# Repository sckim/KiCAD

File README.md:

# KiCad 튜토리얼
대학교 2학년 학생이 KiCad 사용법을 익힐 수 있도록 만든 예제 모음이다. 자세한 설명은 [이 문서](https://docs.google.com/document/d/1ExvIu8tnpRs45NydWLtySDykhyoZ8oFFZSsFo3mHvT8/edit?tab=t.0#heading=h.j3pbzu6m0ixx)를 참고한다.

- 모든 예제는 **KiCad 10** 기준이다.
- 각 예제 폴더에 README가 있다. 번호 순서대로 따라가면 된다.
- KiCad 공식 설명서는 [Docs](./Docs/)에 있다. 처음이라면 *Getting Started in KiCad* 부터 읽는다.

| 폴더 | 내용 |
|---|---|
| [10_Simple_LED](./10_Simple_LED/) | 첫 예제. 회로도에서 PCB, 거버 출력까지 |
| [20_WheatstoneBridge](./20_WheatstoneBridge/) | 회로 시뮬레이션과 PCB를 하나의 회로도로 |
| [22_4bitsFullAdder](./22_4bitsFullAdder/) | 계층 회로도, 논리 IC 보드 |
| [30_Arduino](./30_Arduino/) | Arduino UNO 템플릿과 관련 보드 |
| [70_Simulation](./70_Simulation/) | SPICE 시뮬레이션 전용 예제 |
| [Applications](./Applications/) | 응용 예제(실험 키트, 외부 PCB 가져오기) |
| [Docs](./Docs/) | KiCad 공식 설명서 |

---

## 1. 기본 PCB 예제

### [예제 1. Simple LED](./10_Simple_LED/)
코인 전지로 LED를 켜는 가장 간단한 회로이다. 회로도 작성 → 풋프린트 지정 → PCB 배치·배선 → 거버 출력까지 KiCad의 전체 흐름을 익힌다.
<table>
    <tr>
        <td></td>
        <td></td>
    </tr>
</table>

### [예제 2. Wheatstone Bridge](./20_WheatstoneBridge/)
휘트스톤 브리지를 SPICE로 시뮬레이션하고 PCB로 만든다. 시뮬레이션 전용 부품과 PCB 전용 부품을 한 회로도에서 나누어 쓰는 방법(Exclude from simulation / board)을 익힌다.
<table>
    <tr>
        <td></td>
        <td></td>
    </tr>
</table>

### [예제 3. 4bits Full Adder](./22_4bitsFullAdder/)
반가산기 → 전가산기 → 4비트 덧셈기로 올라가며 **계층 회로도** 를 익힌다. 입력 스위치, 출력 LED, 전원까지 넣어 실제 보드로 만들고, 배선 실습용 PCB와 자동 배선 완성본을 함께 제공한다.
<table>
    <tr><td colspan="2"></td></tr>
    <tr><td colspan="2"></td></tr>
    <tr><td></td><td></td></tr>
</table>

---

## 2. Arduino

### 심볼·풋프린트 편집기: [Arduino_UNO](./30_Arduino/Arduino_UNO/)
KiCad 템플릿으로 Arduino UNO 쉴드의 외곽과 헤더를 만든다.
<table>
    <tr>
        <td></td>
        <td></td>
    </tr>
</table>

### Arduino 관련 프로젝트
[30_Arduino](./30_Arduino/) 폴더에 모아 두었다.
* [Arduino UNO (ATmega328P)](./30_Arduino/UNO_ATmega328P/): Arduino_UNO 템플릿으로 만든 UNO 호환 보드(ATmega328P, 크리스털, 리셋, ICSP, PCB)
* [Arduino UNO I2C LCD](./30_Arduino/Arduino_UNO_I2C_LCD/): Arduino UNO에서 PCF8574 I2C 확장 칩으로 16×2 LCD를 구동하는 회로(회로도만)
* [nRF52840 UNO](./30_Arduino/nRF52840_UNO/): Adafruit Feather nRF52840 Express를 Arduino UNO 레이아웃에 맞춘 보드

---

## 3. 시뮬레이션
PCB 없이 회로도와 시뮬레이션만 다루는 예제를 [70_Simulation](./70_Simulation/)에 모아 두었다. 예제마다 README가 있다.
* [Transient Analysis](./70_Simulation/Transient_Analysis/): 펄스 전원으로 구동하는 RC 회로의 충전과 방전 (`.tran`)
* [Frequency Analysis](./70_Simulation/Frequency_Analysis/): RC 저역통과 필터와 CR 고역통과 필터 비교 (`.ac`)
* [AC Analysis](./70_Simulation/AC_Analysis/): 직렬 RLC 대역통과 필터 (`.ac`)
* [Transistor Bias](./70_Simulation/TransistorBias/): 제조사 2N3904 모델을 쓴 BJT 동작점 (`.op`)
* [Half Adder](./70_Simulation/HalfAdder/): [SpiceModels](./70_Simulation/SpiceModels/)의 74LS 모델을 쓴 디지털 시뮬레이션 (`.tran`)

---

## 4. 응용 예제

### [Analog Discovery 2와 UNO 또는 Adafruit nRF52 Bluefruit 연결](./Applications/Arduino_AD2Kit/)
<table>
    <tr>
        <td></td>
        <td></td>
    </tr>
</table>

### 외부 PCB 가져오기
* [Adafruit nRF52 Bluefruit Feather](./Applications/Adafruit_nRF52_Bluefruit/): [Eagle PCB](https://github.com/adafruit/Adafruit-nRF52-Bluefruit-Feather-PCB)와 [3D 모델](https://github.com/adafruit/Adafruit_CAD_Parts/tree/main/4062%20nRF52840%20Feather)을 KiCad로 가져온 예제

### Texas Instruments EVM 보드 확장
(준비 중)

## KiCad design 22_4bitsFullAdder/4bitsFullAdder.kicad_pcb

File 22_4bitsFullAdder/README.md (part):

# 예제 3. 4bits Full Adder — 계층 회로도(Hierarchical Schematic)

4비트 덧셈기를 만들면서 **계층 회로도**를 익힌다.
반가산기(Half Adder)를 한 장의 시트로 만들고, 이를 두 번 써서 전가산기(Full Adder)를 만든 다음, 전가산기를 네 번 써서 4비트 덧셈기를 만든다.
같은 회로를 여러 번 복사해 그리지 않고 **한 번 그린 시트를 재사용**하는 것이 핵심이다.

<table>
    <tr><td colspan="2"></td></tr>
    <tr><td colspan="2"></td></tr>
    <tr><td></td><td></td></tr>
</table>

> 이 예제는 [예제 1](../10_Simple_LED/)을 마쳤다고 가정한다. 회로도 작성의 기본 조작(심볼 배치, 배선, 레이블)은 예제 1을 참고한다.
> 회로도에는 입력 스위치, 출력 LED, 전원까지 들어 있고, PCB는 부품 배치와 넷 연결까지 되어 있다. **배선은 직접 해 본다**([6장](#6-실제-보드로-만들기)).

---

## 1. 폴더 구성

| 파일 | 설명 |
|---|---|
| `4bitsFullAdder.kicad_pro` | 프로젝트 파일이다. 이 파일을 연다. |
| `4bitsFullAdder.kicad_sch` | **최상위(root) 시트**. 전가산기 시트 4개(`FA0`~`FA3`)와 입출력 버스, 그리고 전원·입력 스위치·출력 LED 회로가 있다. |
| `FullAdder.kicad_sch` | **전가산기 시트**. 반가산기 시트 2개(`HA1`, `HA2`)와 OR 게이트(74HC32)로 이루어진다. |
| `HalfAdder.kicad_sch` | **반가산기 시트**. AND 게이트(74HC08)와 XOR 게이트(74HC86)로 이루어진다. |
| `4bitsFullAdder.kicad_pcb` | PCB. 부품 배치와 넷 연결까지 되어 있고 배선은 되어 있지 않다. |

## 2. 덧셈기의 원리

### 2-1. 반가산기 (Half Adder)
1비트 두 개(A, B)를 더해 합(S)과 올림(C)을 낸다.

| A | B | S (합) | C (올림) |
|---|---|---|---|
| 0 | 0 | 0 | 0 |
| 0 | 1 | 1 | 0 |
| 1 | 0 | 1 | 0 |
| 1 | 1 | 0 | 1 |

```
S = A ⊕ B   (XOR, 74HC86)
C = A · B   (AND, 74HC08)
```

### 2-2. 전가산기 (Full Adder)
아랫자리에서 올라온 올림(Cin)까지 1비트 세 개를 더한다. 반가산기 2개와 OR 게이트 1개로 만든다.

```
HA1:  S1 = A ⊕ B,        C1 = A · B
HA2:  Sum = S1 ⊕ Cin,    C2 = S1 · Cin
Carry = C1 + C2          (OR, 74HC32)
```

```
 A ──┐         S1 ┌─────┐ S ──────────────── Sum
     │ HA1 ├──────┤ HA2 │
 B ──┘     │  Cin ─┤     │ C ──┐
           │       └─────┘     ├── OR ─────── Carry
           └── C1 ─────────────┘
```

### 2-3. 4비트 덧셈기 (Ripple Carry Adder)
전가산기 4개를 이어 붙여, 각 자리의 올림(Carry)을 다음 자리의 Cin으로 넘긴다.

```
          A0 B0      A1 B1      A2 B2      A3 B3
           │  │       │  │       │  │       │  │
 GND(0) → [ FA0 ] → [ FA1 ] → [ FA2 ] → [ FA3 ] → Carry (최종 올림)
             │          │          │          │
           Sum0       Sum1       Sum2       Sum3
```

- 맨 아랫자리 `FA0`의 Cin은 `GND`(0)에 연결한다.
- 올림이 오른쪽 자리로 차례차례 전달된다고 해서 **리플 캐리(ripple carry) 덧셈기**라고 부른다.

---

## 3. 계층 회로도 이해하기

### 3-1. 시트 구조
```
4bitsFullAdder.kicad_sch  (최상위)
├── FA0 ─ FullAdder.kicad_sch ─┬─ HA1 ─ HalfAdder.kicad_sch
│                              └─ HA2 ─ HalfAdder.kicad_sch
├── FA1 ─ FullAdder.kicad_sch   (같은 구조)
├── FA2 ─ FullAdder.kicad_sch   (같은 구조)
└── FA3 ─ FullAdder.kicad_sch   (같은 구조)
```
시트 **파일**은 3개뿐이지만 시트 **인스턴스(사용 횟수)** 는 최상위 1 + 전가산기 4 + 반가산기 8 = 13개이다.

### 3-2. 핵심 개념

| 개념 | 설명 | 이 예제에서 |
|---|---|---|
| **시트 기호 (Sheet Symbol)** | 상위 시트에 놓는 사각형 상자이다. 하위 시트 파일을 가리킨다. | 최상위의 `FA0`~`FA3`, 전가산기 안의 `HA1`, `HA2` |
| **계층 레이블 (Hierarchical Label)** | 하위 시트 안에서 "이 신호를 밖으로 내보낸다/받는다"를 나타낸다. | 반가산기의 `A`, `B`, `S`, `C` / 전가산기의 `A`, `B`, `C`, `Sum`, `Carry` |
| **시트 핀 (Sheet Pin)** | 시트 기호 테두리에 나타나는 핀이다. 하위 시트의 계층 레이블과 **이름이 같아야** 연결된다. | 시트 기호 양옆의 입력/출력 핀 |
| **버스 (Bus)** | 여러 신호를 하나의 굵은 선으로 묶는다. `A[3..0]`은 `A0`, `A1`, `A2`, `A3` 네 신호를 뜻한다. | 최상위의 `A[3..0]`, `B[3..0]`, `Sum[3..0]` |
| **버스 엔트리 (Bus Entry)** | 버스에서 개별 신호를 꺼내는 짧은 사선이다. 꺼낸 선에는 `A0` 같은 레이블을 붙인다. | 최상위의 12개 |

### 3-3. 시트 재사용과 부품 번호
같은 시트 파일을 여러 번 쓰면 **회로는 하나를 공유하지만 부품 번호는 인스턴스마다 따로** 붙는다.
예를 들어 `HalfAdder.kicad_sch`의 AND 게이트는 한 번만 그렸지만, 8개 인스턴스는 각각 다른 IC와 게이트(unit)에 배정된다.

| 인스턴스 | AND (74HC08) | XOR (74HC86) |
|---|---|---|
| FA0 / HA1, HA2 | U1A, U1B | U3A, U3B |
| FA1 / HA1, HA2 | U1C, U1D | U3C, U3D |
| FA2 / HA1, HA2 | U2A, U2B | U4A, U4B |
| FA3 / HA1, HA2 | U2C, U2D | U4C, U4D |

전가산기의 OR 게이트 4개는 `U5A`~`U5D`(74HC32)이다. 한 IC에 게이트가 4개씩 들어 있으므로 게이트 20개가 **IC 5개**에 담긴다. 각 IC의 전원 핀(VCC 14번, GND 7번)은 별도 unit `E`로, 최상위 시트에 배치되어 있다.
그래서 반가산기 시트를 고치면 **8곳 모두에 한꺼번에 반영된다.**

---

## 4. 예제 살펴보기

1. `4bitsFullAdder.kicad_pro`를 열고 회로도 편집기를 연다.
2. 왼쪽 **계층 탐색기(Hierarchy Navigator)** 에서 시트 트리를 확인한다. 보이지 않으면 **View → Show Hierarchy Navigator** 를 켠다.
3. 시트 기호(`FA0`)를 **더블클릭**하면 하위 시트로 들어간다. 계층 탐색기에서 최상위를 클릭하면 다시 올라온다.
4. `FA0` 안의 `HA1`로 들어가 부품 번호를 확인하고, 다시 나와 `FA1` 안의 `HA1`로 들어가 번호가 다른지 비교한다.
5. 한 신호가 어디로 이어지는지 보려면 선을 클릭한 뒤 **`` ` `` (백틱) 키**로 넷 전체를 강조 표시한다.

---

## 5. 처음부터 직접 만들어 보기

아래(반가산기)에서 위(4비트)로 올라가며 만든다.

### 5-1. 반가산기 시트 만들기
1. 새 프로젝트 `My_Adder`를 만든다. 최상위 시트는 잠시 비워 둔다.
2. **Place → Add Hierarchical Sheet** 를 선택하고 최상위 시트에 사각형을 그린다.
   창이 뜨면 **Sheet name**은 `HA`, **File name**은 `HalfAdder.kicad_sch`로 입력한다.
3. 시트 기호를 더블클릭해 들어간 뒤, AND 게이트와 XOR 게이트를 배치한다. 심볼은 `74xx:74LS08`, `74xx:74LS86`을 쓰고 Value를 `74HC08`, `74HC86`으로 바꾼다(핀 배치가 같다).
4. **Place → Add Hierarchical Label** 로 입력 `A`, `B`(Shape: Input)와 출력 `S`, `C`(Shape: Output)를 배치하고 게이트에 연결한다.
   - `A`, `B` → AND와 XOR의 입력에 각각 연결
   - XOR 출력 → `S`, AND 출력 → `C`

### 5-2. 시트 핀 동기화
1. 최상위로 돌아오면 시트 기호에는 아직 핀이 없다.
2. 시트 기호를 오른쪽 클릭 → **Sync Sheet Pins** 를 실행하고, 하위 시트의 계층 레이블을 시트 핀으로 가져온다.
3. 핀을 시트 테두리의 원하는 위치(입력은 왼쪽, 출력은 오른쪽)로 옮긴다.

> 시트 핀과 계층 레이블은 **이름이 한 글자라도 다르면 연결되지 않는다.** 대소문자도 구분한다.

### 5-3. 전가산기 시트 만들기
1. 최상위에 새 시트 기호 `FA`(파일 `FullAdder.kicad_sch`)를 만들고 들어간다.
2. 전가산기 시트 안에 시트 기호를 2개 만들고, 둘 다 **File name을 `HalfAdder.kicad_sch`** 로 지정한다. 이름은 `HA1`, `HA2`로 한다.
   - 이미 있는 파일 이름을 입력하면 KiCad가 "기존 시트를 사용할지" 묻는다. **사용한다**를 선택한다.
3. `74HC32`(OR, 심볼은 `74xx:74LS32`)를 배치하고, [2-2절](#2-2-전가산기-full-adder)의 식대로 연결한다.
   - `A`, `B` → HA1 입력
   - HA1의 **S** 와 `C`(Cin) → HA2 입력
   - HA2의 **S** → `Sum`
   - HA1의 **C** 와 HA2의 **C** → OR 입력, OR 출력 → `Carry`
4. 계층 레이블 `A`, `B`, `C`(입력)와 `Sum`, `Carry`(출력)를 붙인다.
5. 반가산기 시트 기호는 최상위에서 지운다. 반가산기는 이제 전가산기 안에서만 쓴다.

### 5-4. 최상위 시트 완성
1. 최상위에 전가산기 시트 기호 4개(`FA0`~`FA3`, 모두 `FullAdder.kicad_sch`)를 배치한다. 하나를 만들고 복사(`Ctrl+C`, `Ctrl+V`)해도 된다.
2. 올림을 연결한다. `FA0`의 `C` → `GND`, `FA0`의 `Carry` → `FA1`의 `C`, … `FA2`의 `Carry` → `FA3`의 `C`
3. **Place → Add Bus** 로 버스를 그리고, 버스에 전역 레이블 `A[3..0]`을 붙인다. `B[3..0]`, `Sum[3..0]`도 같은 방법으로 만든다.
4. **Place → Add Wire to Bus Entry** 로 버스에서 선을 꺼내고, 각 선에 `A0`, `A1`, … 레이블을 붙여 각 전가산기의 핀에 연결한다.
5. 마지막 자리의 `Carry`에는 `Cout` 같은 레이블을 붙여 최종 올림으로 쓴다.

### 5-5. 번호 매기기와 검사
1. **Tools → Annotate Schematic** 에서 범위를 **Entire schematic**(전체 회로도)으로 두고 실행한다. 모든 인스턴스에 서로 다른 번호가 붙는다.
2. **Inspect → Electrical Rules Checker** 로 ERC를 실행한다.
3. 진리표로 동작을 확인한다. 예) `A = 0011(3)`, `B = 0101(5)` → `Sum = 1000(8)`, `Cout = 0`

---

## 6. 실제 보드로 만들기

### 6-1. 회로도에 추가된 부분 (최상위 시트)
덧셈기만으로는 실제 보드가 동작하지 않는다. 최상위 시트에 다음을 추가했다.

| 부품 | 역할 |
|---|---|
| `J1` (2핀 헤더) + `PWR_FLAG` | 5 V 전원 입력. `PWR_FLAG`는 ERC에 전원이 공급됨을 알린다. |
| `U1E`~`U5E` + `C1`~`C5` (100 nF) | 각 IC의 전원 unit과 **디커플링 커패시터**. 커패시터는 IC 전원 핀 가까이 둔다. |
| `SW1` (8비트 DIP 스위치) + `RN1` (10 kΩ ×8) | 입력 A0~A3, B0~B3. 스위치를 켜면 VCC(1), 끄면 풀다운 저항으로 GND(0)가 된다. |
| `R1`~`R5` (1 kΩ) + `D1`~`D5` (LED) | 출력 Sum0~Sum3, Cout 표시. 출력이 1이면 LED가 켜진다. |
| `J2` (6핀 헤더) | 출력 Sum0~Sum3, Cout, GND. Analog Discovery 2 같은 장비로 측정할 수 있다. |

> **왜 74HC인가?** 74LS 계열은 출력이 High일 때 흘릴 수 있는 전류가 작아(0.4 mA) LED를 직접 켜기 어렵다. 74HC 계열은 High/Low 모두 수 mA를 낼 수 있고, 입력에 큰 풀다운 저항(10 kΩ)을 써도 된다. 74HC08/86/32는 74LS08/86/32와 핀 배치가 같다.

### 6-2. PCB 배선하기
`4bitsFullAdder.kicad_pcb`를 열면 부품이 배치되어 있고 래츠네스트(가는 선)가 연결할 곳을 보여 준다. 보드 크기는 110 mm × 70 mm이고, 뒷면(`B.Cu`)에는 GND 동박 영역이 있다.

1. [예제 1의 4-7절](../10_Simple_LED/README.md#4-처음부터-직접-만들어-보기)처럼 `X`로 배선한다. 전원(VCC)은 0.5 mm 이상, 신호는 0.25 mm 정도로 한다.
2. GND는 뒷면 동박 영역으로 연결되므로, 앞면(`F.Cu`)에 신호와 VCC를 먼저 배선하고 막히는 곳만 비아로 뒷면을 쓴다.
3. 배선이 끝나면 `B`로 동박 영역을 다시 채우고, **Inspect → Design Rules Checker** 에서 **Unconnected Items가 0개**가 될 때까지 반복한다.

> 회로도를 고친 뒤에는 **Tools → Update PCB from Schematic** (`F8`)으로 PCB에 반영한다. 부품 배치는 그대로 유지된다.

**참고용 완성본** — `4bitsFullAdder_routed.kicad_pcb`는 같은 배치를 자동 배선 프로그램 [Freerouting](https://github.com/freerouting/freerouting)으로 배선한 파일이다(DRC 오류 0개, 미연결 0개). 직접 배선한 뒤 비교해 본다. 프로젝트 창이 아니라 PCB 편집기의 **File → Open** 으로 연다.

| 규칙 | 값 |
|---|---|
| 신호선 (Default 넷 클래스) | 폭 0.3 mm, 간격 0.25 mm |
| 전원선 (Power 넷 클래스: VCC, GND) | 폭 0.6 mm |
| 비아 | 지름 0.8 mm / 드릴 0.4 mm |

넷 클래스는 **File → Board Setup → Net Classes** 에서 확인할 수 있다.

### 6-3. 더 생각해 볼 점
- **시뮬레이션** — 이 예제에는 SPICE 설정이 없다. 74LS 게이트 시뮬레이션은 [70_Simulation/HalfAdder](../70_Simulation/HalfAdder/)를 참고한다.
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
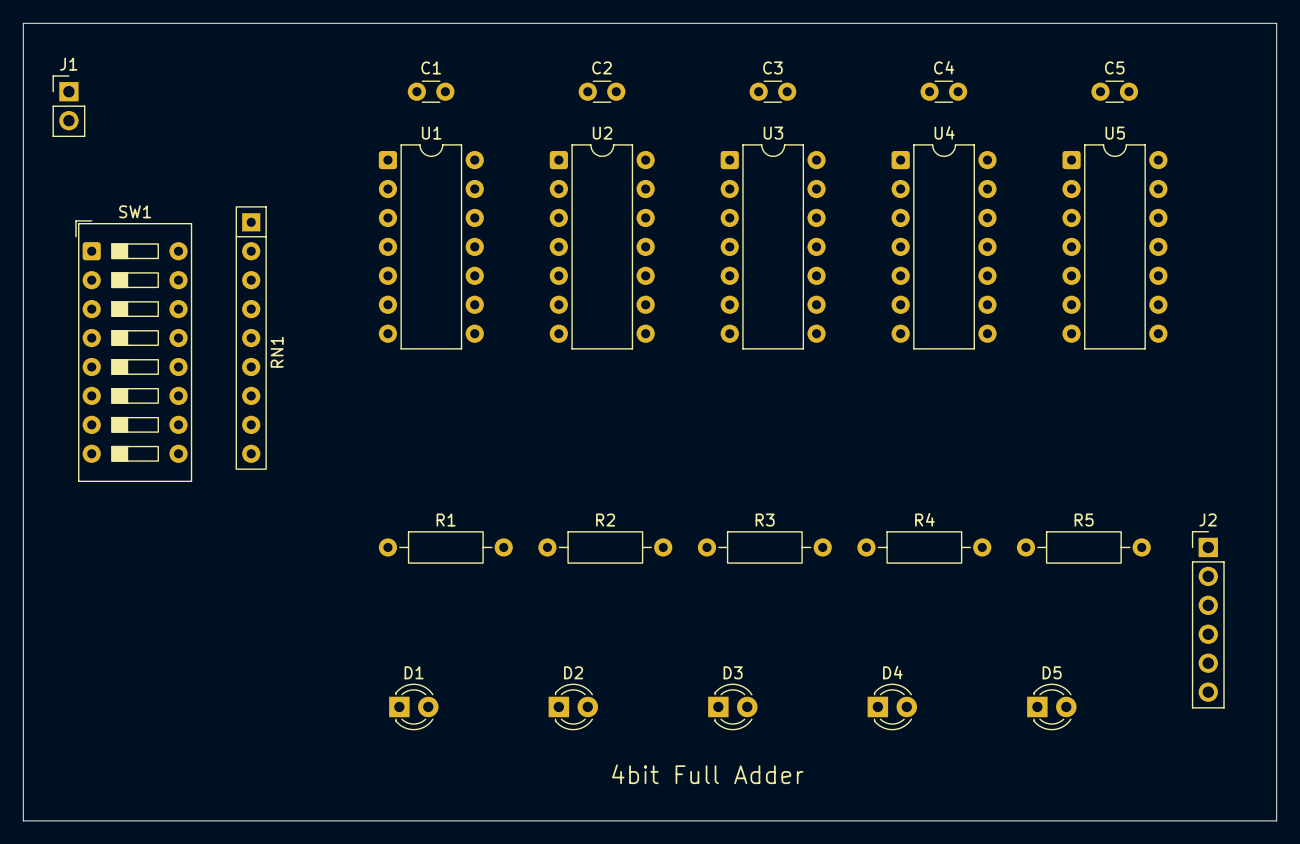
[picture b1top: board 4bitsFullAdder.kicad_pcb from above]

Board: 2 copper layers, 110.0 x 70.0 mm, 24 parts (0 on the bottom side), 35 nets, no tracks yet.

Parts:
C1, C2, C3, C4, C5: 100n; C_Disc_D3.0mm_W1.6mm_P2.50mm
D1, D2, D3, D4, D5: LED; LED_D3.0mm
J1: 5V_IN; PinHeader_1x02_P2.54mm_Vertical
J2: OUT; PinHeader_1x06_P2.54mm_Vertical
R1, R2, R3, R4, R5: 1k; R_Axial_DIN0207_L6.3mm_D2.5mm_P10.16mm_Horizontal
RN1: 10k; R_Array_SIP9
SW1: SW_DIP_x08; SW_DIP_SPSTx08_Slide_9.78x22.5mm_W7.62mm_P2.54mm
U1, U2: 74HC08; DIP-14_W7.62mm
U3, U4: 74HC86; DIP-14_W7.62mm
U5: 74HC32; DIP-14_W7.62mm

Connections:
/Cout: J2.5, R5.1, U5.11
/FA0/Carry: U1.12, U3.13, U5.3
/FA0/HA1/C: U1.3, U5.2
/FA0/HA1/S: U1.5, U3.3, U3.4
/FA0/HA2/C: U1.6, U5.1
/FA1/Carry: U2.4, U4.5, U5.6
/FA1/HA1/C: U1.8, U5.5
/FA1/HA1/S: U1.13, U3.8, U3.12
/FA1/HA2/C: U1.11, U5.4
/FA2/Carry: U2.12, U4.13, U5.8
/FA2/HA1/C: U2.3, U5.10
/FA2/HA1/S: U2.5, U4.3, U4.4
/FA2/HA2/C: U2.6, U5.9
/FA3/HA1/C: U2.8, U5.13
/FA3/HA1/S: U2.13, U4.8, U4.12
/FA3/HA2/C: U2.11, U5.12
/LED_Cout: D5.2, R5.2
/LED_Sum0: D1.2, R1.2
/LED_Sum1: D2.2, R2.2
/LED_Sum2: D3.2, R3.2
/LED_Sum3: D4.2, R4.2
A0: RN1.2, SW1.16, U1.2, U3.1
A1: RN1.3, SW1.15, U1.10, U3.9
A2: RN1.4, SW1.14, U2.2, U4.1
A3: RN1.5, SW1.13, U2.10, U4.9
B0: RN1.6, SW1.12, U1.1, U3.2
B1: RN1.7, SW1.11, U1.9, U3.10
B2: RN1.8, SW1.10, U2.1, U4.2
B3: RN1.9, SW1.9, U2.9, U4.10
GND: C1.2, C2.2, C3.2, C4.2, C5.2, D1.1, D2.1, D3.1, D4.1, D5.1, J1.2, J2.6, RN1.1, U1.4, U1.7, U2.7, U3.5, U3.7, U4.7, U5.7
Sum0: J2.1, R1.1, U3.6
Sum1: J2.2, R2.1, U3.11
Sum2: J2.3, R3.1, U4.6
Sum3: J2.4, R4.1, U4.11
VCC: C1.1, C2.1, C3.1, C4.1, C5.1, J1.1, SW1.1, SW1.2, SW1.3, SW1.4, SW1.5, SW1.6, SW1.7, SW1.8, U1.14, U2.14, U3.14, U4.14, U5.14

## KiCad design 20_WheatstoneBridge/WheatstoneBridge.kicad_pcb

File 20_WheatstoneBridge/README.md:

# 예제 2. Wheatstone Bridge — 회로 시뮬레이션과 PCB

휘트스톤 브리지(Wheatstone Bridge)는 저항 4개로 두 개의 분압기를 만들고, 두 중간점의 전압 차이로 저항의 균형 여부를 판단하는 회로이다.
이 예제에서는 [예제 1](../10_Simple_LED/)의 흐름(회로도 → PCB)에 더해 **KiCad에 내장된 SPICE 시뮬레이터(ngspice)** 로 회로를 먼저 계산해 보는 방법을 익힌다.

<table>
    <tr>
        <td></td>
        <td></td>
    </tr>
</table>

> 이 예제는 [예제 1](../10_Simple_LED/)을 마쳤다고 가정한다. 회로도 그리기, 풋프린트 지정, PCB 배선 방법은 예제 1을 참고한다.

---

## 1. 폴더 구성

| 파일 | 설명 |
|---|---|
| `WheatstoneBridge.kicad_pro` | 프로젝트 파일이다. 이 파일을 연다. |
| `WheatstoneBridge.kicad_sch` | 회로도 (시뮬레이션 설정 포함) |
| `WheatstoneBridge.wbk` | 시뮬레이터 작업 파일(workbook)이다. 해석 종류와 명령이 저장되어 있다. |
| `WheatstoneBridge.kicad_pcb` | PCB 레이아웃 |
| `gerber/` | PCB 제작 파일(거버, 드릴) |

## 2. 회로 이해하기

전원(10 V)과 GND 사이에 분압기 두 개가 나란히 연결되어 있다.

```
         VCC (10 V)
        ┌────┴────┐
        R1 500Ω   R2 1kΩ
        │         │
  A ────┤         ├──── B
        │   D1    │
        │ A ▶|─ K │          A: LED 애노드 쪽, B: LED 캐소드 쪽
        │         │
       RV1 75Ω   R3 150Ω
        └────┬────┘
            GND
```

| 참조 번호 | 부품 | 값 | 역할 |
|---|---|---|---|
| V1 | DC 전압원 (`Simulation_SPICE:VDC`) | 10 V | **시뮬레이션 전용** 전원 (Exclude from board) |
| BT1 | 전지 (`Device:Battery_Cell`) | — | **PCB 전용** 전원 (Exclude from simulation) |
| R1, RV1 | 저항, 가변저항(트리머) | 500 Ω, 75 Ω | 왼쪽 분압기 → 점 A |
| R2, R3 | 저항 | 1 kΩ, 150 Ω | 오른쪽 분압기 → 점 B |
| D1 | LED (`Device:LED`) + 다이오드 모델 | — | A와 B 사이 전압 차 검출. 시뮬레이션과 PCB에 모두 쓰인다 |

### 브리지 평형 조건
두 분압기의 비율이 같으면 A와 B의 전압이 같아지고 LED에는 전류가 흐르지 않는다. 이를 **평형(balanced)** 상태라고 한다.

```
R1 / RV1 = R2 / R3   →   RV1 = R1 × R3 / R2 = 500 × 150 / 1000 = 75 Ω
```

손으로 계산한 각 점의 전압은 다음과 같다.

```
V_B = 10 V × R3 / (R2 + R3)   = 10 × 150 / 1150 ≈ 1.30 V   (고정)
V_A = 10 V × RV1 / (R1 + RV1)                                (RV1에 따라 변함)
```

| RV1 `pos` | A–GND 사이 저항 | V_A | V_A − V_B | 상태 |
|---|---|---|---|---|
| 0 | 75 Ω | 1.30 V | 0 V | 평형 |
| 0.5 | 37.5 Ω | 0.70 V | −0.61 V | 불평형 (LED 역방향) |
| 1 | 0 Ω | 0 V | −1.30 V | 불평형 (LED 역방향) |

`pos`는 가변저항 와이퍼의 위치(0~1)이다. 이 회로에서는 `pos = 0`일 때 A–GND 사이가 75 Ω(전체)이 된다.

시뮬레이션을 돌리기 전에 이렇게 **먼저 손으로 예상값을 계산해 두고**, 시뮬레이션 결과와 비교하는 습관을 들인다.

---

## 3. 시뮬레이션 해 보기

### 3-1. 시뮬레이션용 부품의 특징
시뮬레이션하려면 모든 부품에 **SPICE 모델**이 있어야 한다. 이 예제에서 눈여겨볼 점은 다음과 같다.

- **`GND` (접지 기호)** — SPICE의 기준점(0 V)이 된다. 시뮬레이션 회로에는 접지가 반드시 하나 이상 있어야 한다. 시뮬레이션만 하는 회로라면 `Simulation_SPICE:0` 기호를 써도 된다.
- **`Simulation_SPICE:VDC`** — DC 전압원이다. Value에 전압(`10`)을 적는다.
- **`Device:R`** — 일반 저항은 따로 설정하지 않아도 KiCad가 자동으로 SPICE 저항으로 바꾼다.
- **`Device:R_Potentiometer` (RV1)** — 가변저항 모델(`POT`)을 쓰며, 전체 저항 `r=75`와 와이퍼 위치 `pos`(0~1)를 파라미터로 가진다.
- **`Device:LED` (D1)** — PCB에 쓰는 실제 LED 심볼에 기본 다이오드 모델(`Sim.Device = D`, `Sim.Pins = 1=K 2=A`)을 붙였다. 실제 LED의 특성과는 다르므로 "전류가 흐르는가"를 보는 정도로만 쓴다.

부품의 모델은 부품을 더블클릭(`E`) → **Simulation Model…** 버튼에서 확인하고 바꿀 수 있다.

### 3-2. 시뮬레이터 실행
1. 회로도 편집기에서 **Inspect → Simulator** 를 연다.
2. 저장된 작업 파일(`WheatstoneBridge.wbk`)이 자동으로 열린다. 해석 종류는 **DC 동작점 해석(`.op`, Operating Point)** 이다.
   - 새로 만들 때는 **Simulation → New Analysis Tab** 에서 *Operating Point* 를 고른다.
3. **Run Simulation** (▶ 버튼)을 누른다.
4. 결과 목록에서 각 넷의 전압(`V(...)`)과 소자 전류(`I(...)`)를 확인한다.
   - 점 A는 `Net-(D1-A)`, 점 B는 `Net-(D1-K)` 넷이다. 넷 이름이 길다면 회로도에서 두 점에 넷 레이블(`L`)로 `A`, `B` 같은 이름을 붙이면 결과를 읽기 쉬워진다.
5. 2장에서 계산한 V_A, V_B와 비교한다.

### 3-3. 직접 바꿔 보기
1. RV1을 더블클릭 → **Simulation Model…** 에서 `pos` 값을 `0`, `0.5`, `1`로 바꿔 가며 다시 시뮬레이션한다.
2. 각 경우의 V_A, V_B, D1 전류를 표로 정리하고 2장의 계산값과 비교한다.
3. **과제:** 현재 값으로는 V_A가 V_B보다 커지지 않아 LED가 켜지지 않는다. LED에 순방향 전류가 흐르게 하려면 어떤 저항값을 바꿔야 하는지 계산하고, 시뮬레이션으로 확인한다.

---

## 4. PCB 살펴보기

| 항목 | 값 |
|---|---|
| 보드 크기 | 120 mm × 87.5 mm |
| 배선 폭 | 0.2 mm |
| GND 동박 영역 | 앞면(`F.Cu`) |
| 전원 | CR2032 전지 홀더 (`Battery:BatteryHolder_Keystone_1060_1x2032`) |
| 가변저항 | 다회전 트리머 (`Potentiometer_THT:Potentiometer_Bourns_3296W_Vertical`) |
| LED | 5 mm LED (`LED_THT:LED_D5.0mm`) |

배치·배선·DRC·거버 출력 방법은 [예제 1의 4장](../10_Simple_LED/README.md#4-처음부터-직접-만들어-보기)과 같다.

### 하나의 회로도로 시뮬레이션과 PCB를 함께 하기
시뮬레이션에 필요한 부품과 PCB에 필요한 부품은 다를 수 있다. 이 예제의 전원이 그렇다. 시뮬레이션에는 이상적인 전압원(`V1`)이, 실제 보드에는 전지 홀더(`BT1`)가 필요하다.
KiCad에서는 부품 속성(`E`)의 체크박스로 부품마다 용도를 정한다.

| 부품 | Exclude from simulation | Exclude from board | 결과 |
|---|---|---|---|
| `V1` (전압원) | ☐ | ☑ | 시뮬레이션에만 쓰이고 PCB에는 나타나지 않는다 |
| `BT1` (전지) | ☑ | ☐ | PCB에만 쓰이고 시뮬레이션에서는 빠진다 |
| `D1` (LED), 저항들 | ☐ | ☐ | 둘 다에 쓰인다. `D1`은 실제 LED 심볼에 시뮬레이션 모델을 붙였다 |

이렇게 하면 회로도를 고친 뒤 **Update PCB from Schematic (`F8`)** 을 실행해도 PCB가 그대로 유지된다(회로도와 PCB 일치 검사 결과 불일치 0개).

> 시뮬레이션은 10 V 전원으로 계산하지만, PCB의 전지 홀더는 CR2032(3 V)용이다. 실제로 보드를 만든다면 전원 전압을 맞추어 저항값을 다시 계산하거나, 9 V 전지 커넥터 같은 다른 전원을 고려한다.

---

## 5. 자주 하는 실수

| 증상 | 원인과 해결 |
|---|---|
| 시뮬레이션 시 접지(ground)가 없다는 오류 | `Simulation_SPICE:0` 기호(또는 `GND`)가 회로에 없다. 하나 이상 연결한다. |
| 부품에 모델이 없다는 오류 | 해당 부품의 **Simulation Model…** 에서 모델을 지정하거나, 시뮬레이션에서 제외(Exclude from simulation)한다. |
| 결과가 손 계산과 크게 다름 | 저항 단위를 확인한다. `1k` = 1000 Ω, `1m` = 0.001 Ω(밀리)이다. 메가옴은 `1Meg`로 쓴다. |
| `F8` 후 PCB 부품이 사라짐 | 회로도에 없거나 **Exclude from board** 가 체크된 부품은 PCB에서 삭제된다. 4장의 표를 참고한다. |

## 6. 다음 단계
- [70_Simulation](../70_Simulation/): AC 해석, 주파수 해석, 과도 해석 등 시뮬레이션 전용 예제
- [Docs](../Docs/): *Schematic Editor* 매뉴얼의 시뮬레이터 장

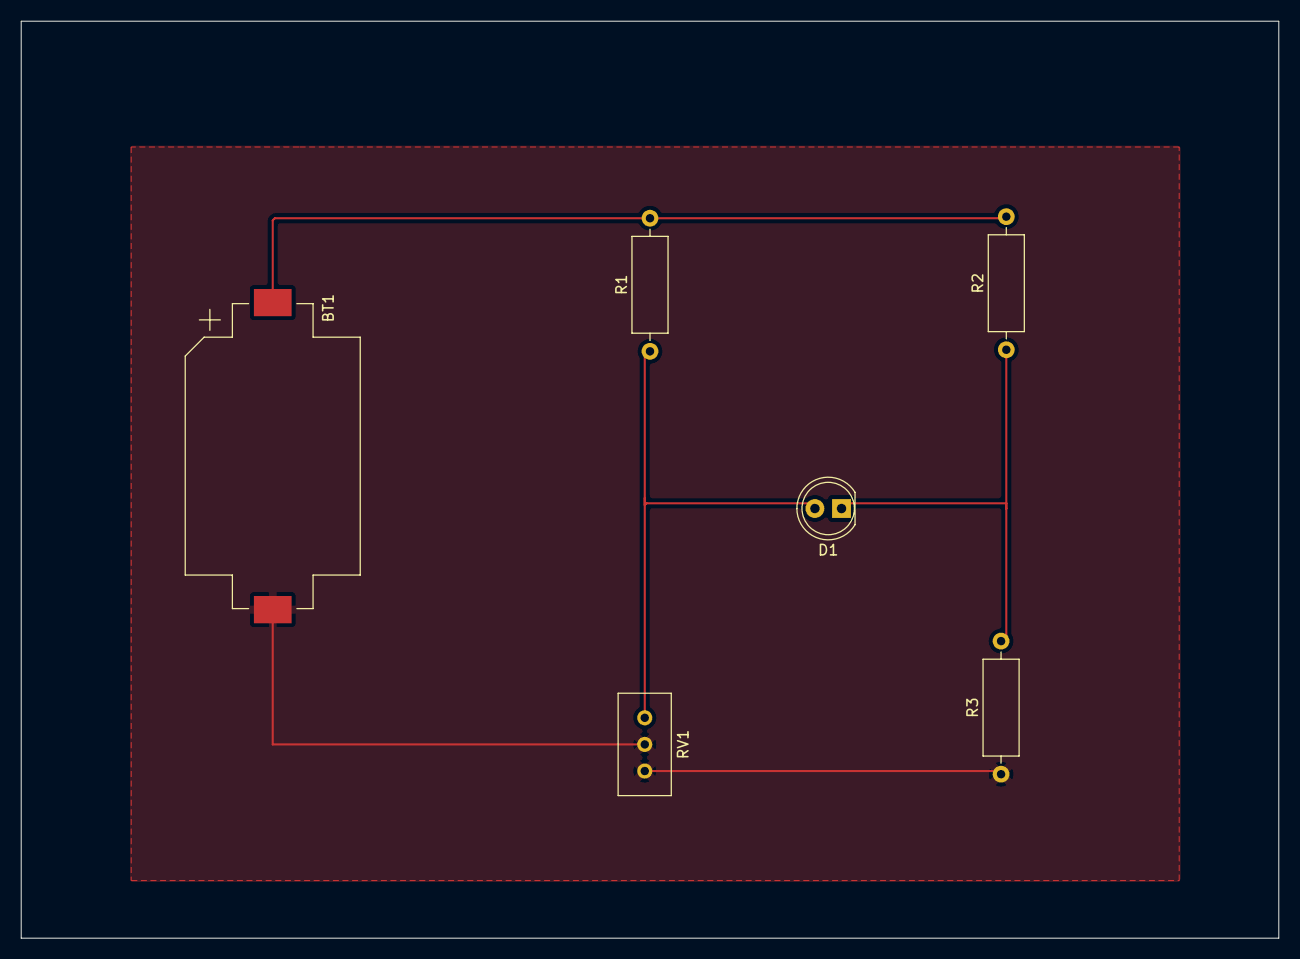
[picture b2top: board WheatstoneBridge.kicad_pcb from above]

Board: 2 copper layers, 120.0 x 87.5 mm, 6 parts (0 on the bottom side), 4 nets.

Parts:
BT1: 10; BatteryHolder_Keystone_1060_1x2032
D1: LED; LED_D5.0mm
R1: 500; R_Axial_DIN0309_L9.0mm_D3.2mm_P12.70mm_Horizontal
R2: 1k; R_Axial_DIN0309_L9.0mm_D3.2mm_P12.70mm_Horizontal
R3: 150; R_Axial_DIN0309_L9.0mm_D3.2mm_P12.70mm_Horizontal
RV1: 75; Potentiometer_Bourns_3296W_Vertical

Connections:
GND: BT1.2 (-), R3.1, RV1.1, RV1.2
unnamed: D1.2 (A), R1.1, RV1.3
unnamed: D1.1 (K), R2.1, R3.2
VCC: BT1.1 (+), R1.2, R2.2

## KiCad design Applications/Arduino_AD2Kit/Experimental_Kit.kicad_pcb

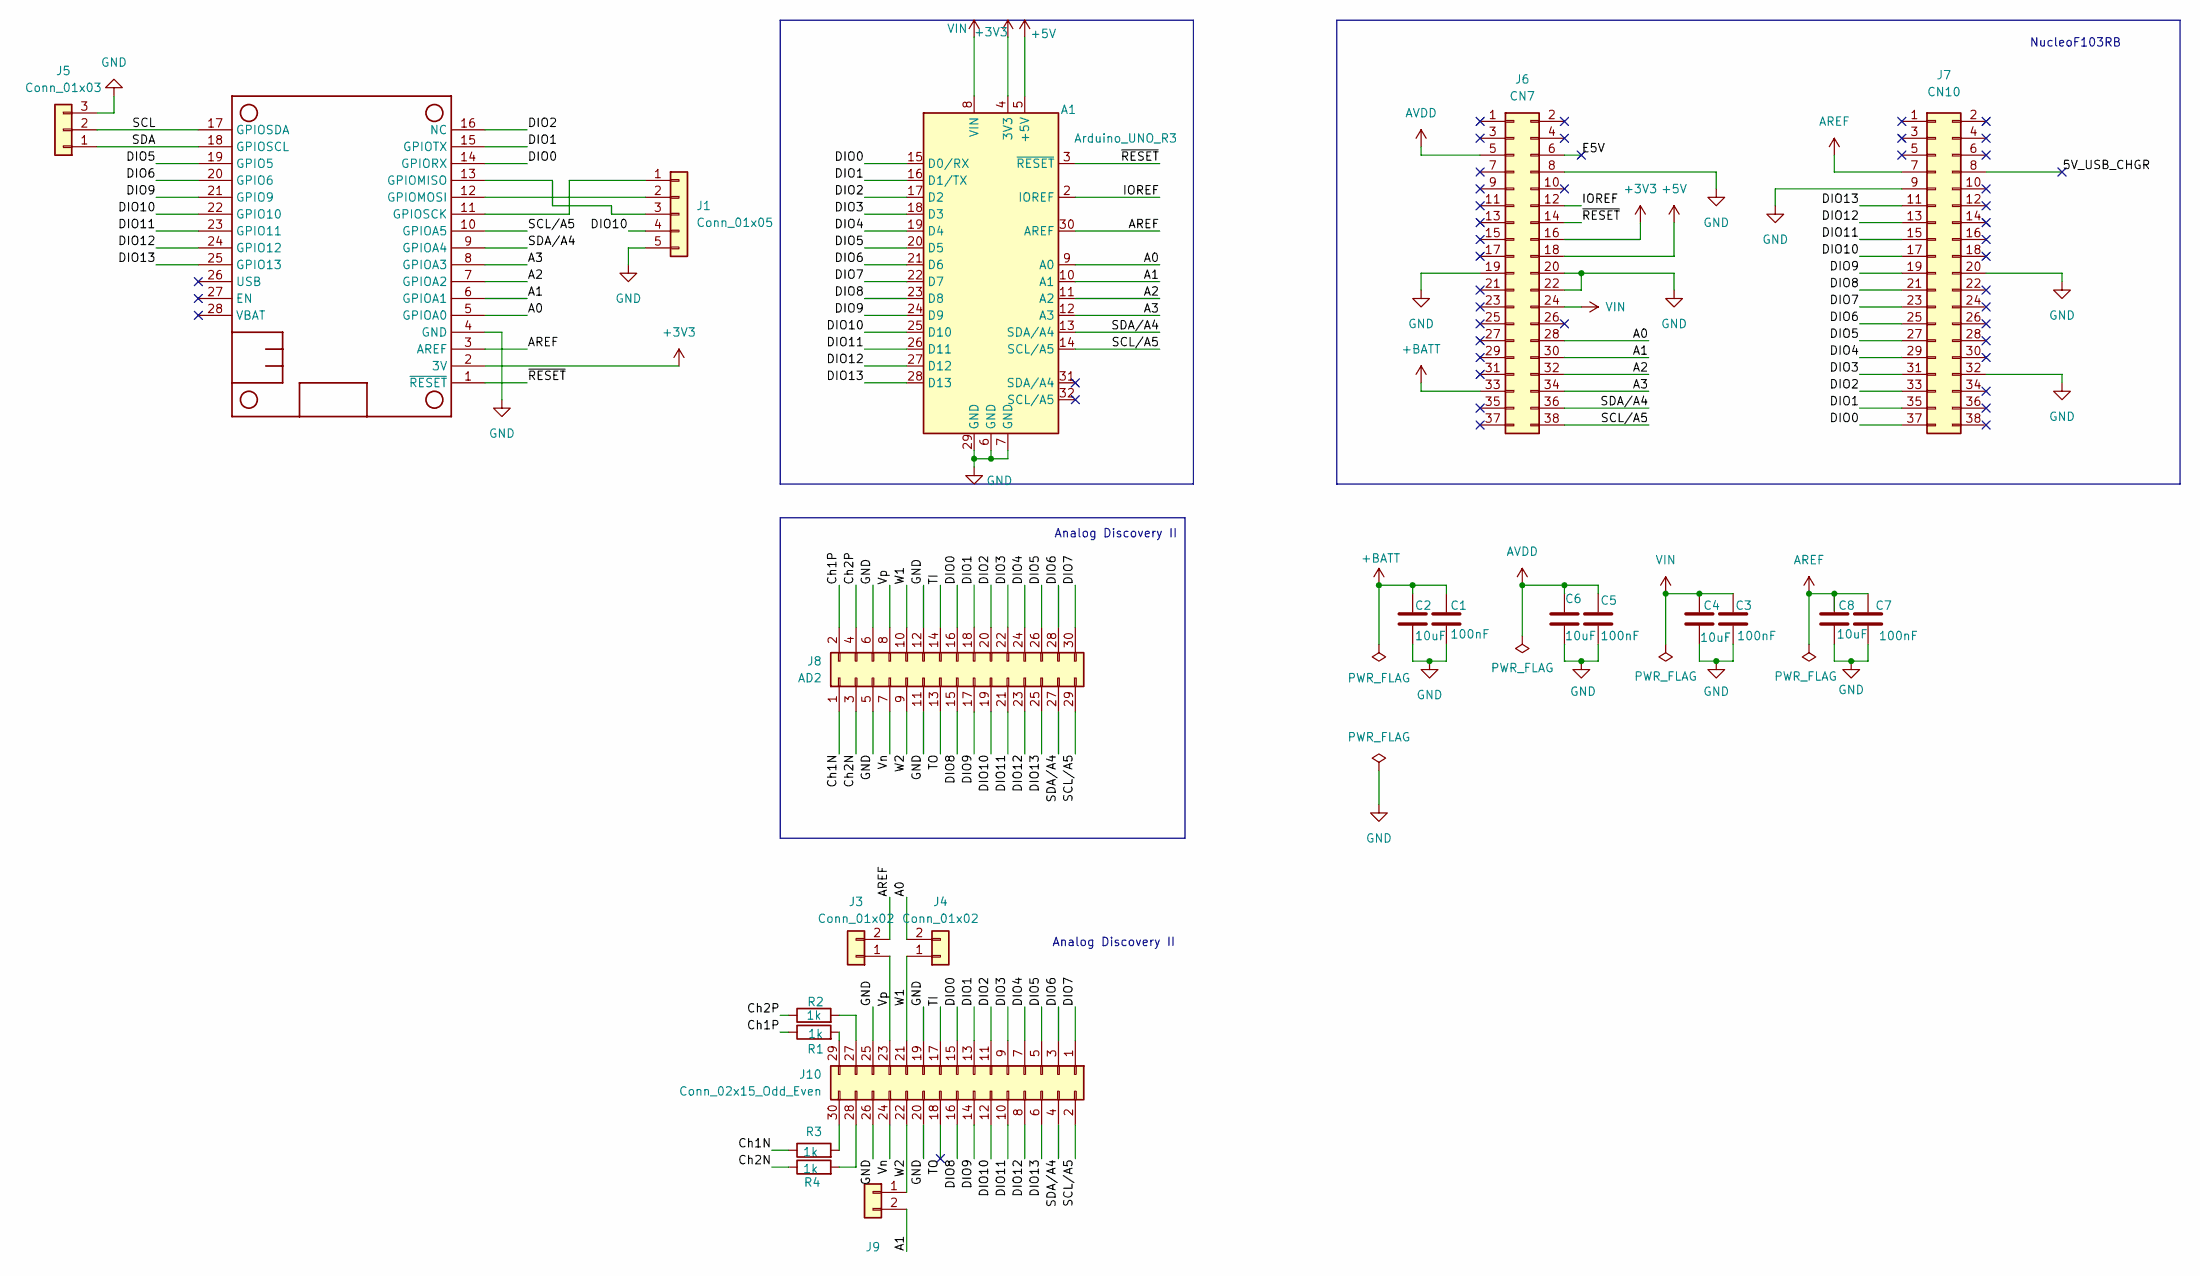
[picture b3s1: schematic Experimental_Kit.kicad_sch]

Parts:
A1: Arduino_UNO_R3
C1, C7: 100nF; C_1206_3216Metric
C2: 10uF; C_0805_2012Metric
C3, C5: 100nF; C_0805_2012Metric
C4, C6, C8: 10uF; C_1206_3216Metric
J1: Conn_01x05; PinHeader_1x05_P2.54mm_Vertical
J3, J4, J9: Conn_01x02; PinHeader_1x02_P2.54mm_Vertical
J5: Conn_01x03; PinHeader_1x03_P2.54mm_Vertical
J6: CN7; PinSocket_2x19_P2.54mm_Vertical
J7: CN10; PinSocket_2x19_P2.54mm_Vertical
J8: AD2; PinSocket_2x15_P2.54mm_Vertical
J10: Conn_02x15_Odd_Even; PinSocket_2x15_P2.54mm_Horizontal
MS1: FEATHERWING_NODIM
R1, R2, R3, R4: 1k; R_0805_2012Metric

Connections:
+3V3: A1.4 (3V3), J6.16, MS1.2 (3V)
+5V: A1.5 (+5V), J6.18
+BATT: C1.1, C2.1, J6.33
/5V_USB_CHGR: J7.8
/A0: A1.9 (A0), J4.2, J6.28, MS1.5 (GPIOA0)
/A1: A1.10 (A1), J6.30, J9.2, MS1.6 (GPIOA1)
/A2: A1.11 (A2), J6.32, MS1.7 (GPIOA2)
/A3: A1.12 (A3), J6.34, MS1.8 (GPIOA3)
/Ch1N: J8.1, R3.1
/Ch1P: J8.2, R1.1
/Ch2N: J8.3, R4.1
/Ch2P: J8.4, R2.1
/DIO0: A1.15 (D0/RX), J7.37, J8.16, J10.15, MS1.14 (GPIORX)
/DIO1: A1.16 (D1/TX), J7.35, J8.18, J10.13, MS1.15 (GPIOTX)
/DIO2: A1.17 (D2), J7.33, J8.20, J10.11, MS1.16 (NC)
/DIO3: A1.18 (D3), J7.31, J8.22, J10.9
/DIO4: A1.19 (D4), J7.29, J8.24, J10.7
/DIO5: A1.20 (D5), J7.27, J8.26, J10.5, MS1.19 (GPIO5)
/DIO6: A1.21 (D6), J7.25, J8.28, J10.3, MS1.20 (GPIO6)
/DIO7: A1.22 (D7), J7.23, J8.30, J10.1
/DIO8: A1.23 (D8), J7.21, J8.15, J10.16
/DIO9: A1.24 (D9), J7.19, J8.17, J10.14, MS1.21 (GPIO9)
/DIO10: A1.25 (D10), J1.4, J7.17, J8.19, J10.12, MS1.22 (GPIO10)
/DIO11: A1.26 (D11), J7.15, J8.21, J10.10, MS1.23 (GPIO11)
/DIO12: A1.27 (D12), J7.13, J8.23, J10.8, MS1.24 (GPIO12)
/DIO13: A1.28 (D13), J7.11, J8.25, J10.6, MS1.25 (GPIO13)
/E5V: J6.6
/IOREF: A1.2 (IOREF), J6.12
/SCL: J5.2, MS1.17 (GPIOSDA)
/SCL/A5: A1.14 (SCL/A5), J6.38, J8.29, J10.2, MS1.10 (GPIOA5)
/SDA: J5.1, MS1.18 (GPIOSCL)
/SDA/A4: A1.13 (SDA/A4), J6.36, J8.27, J10.4, MS1.9 (GPIOA4)
/TI: J8.14, J10.17
/TO: J8.13, J10.18
/Vn: J8.7, J10.24
/Vp: J3.1, J8.8, J10.23
/W1: J4.1, J8.10, J10.21
/W2: J8.9, J9.1, J10.22
/~RESET: A1.3 (~RESET), J6.14, MS1.1 (~RESET)
AREF: A1.30 (AREF), C7.1, C8.1, J3.2, J7.7, MS1.3 (AREF)
AVDD: C5.1, C6.1, J6.5
GND: A1.6 (GND), A1.7 (GND), A1.29 (GND), C1.2, C2.2, C3.2, C4.2, C5.2, C6.2, C7.2, C8.2, J1.5, J5.3, J6.8, J6.19, J6.20, J6.22, J7.9, J7.20, J7.32, J8.5, J8.6, J8.11, J8.12, J10.19, J10.20, J10.25, J10.26, MS1.4 (GND)
unnamed: J1.1, MS1.11 (GPIOSCK)
unnamed: J1.2, MS1.12 (GPIOMOSI)
unnamed: J1.3, MS1.13 (GPIOMISO)
unnamed: J10.27, R2.2
unnamed: J10.28, R4.2
unnamed: J10.29, R1.2
unnamed: J10.30, R3.2
VIN: A1.8 (VIN), C3.1, C4.1, J6.24

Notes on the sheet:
Analog Discovery II
NucleoF103RB

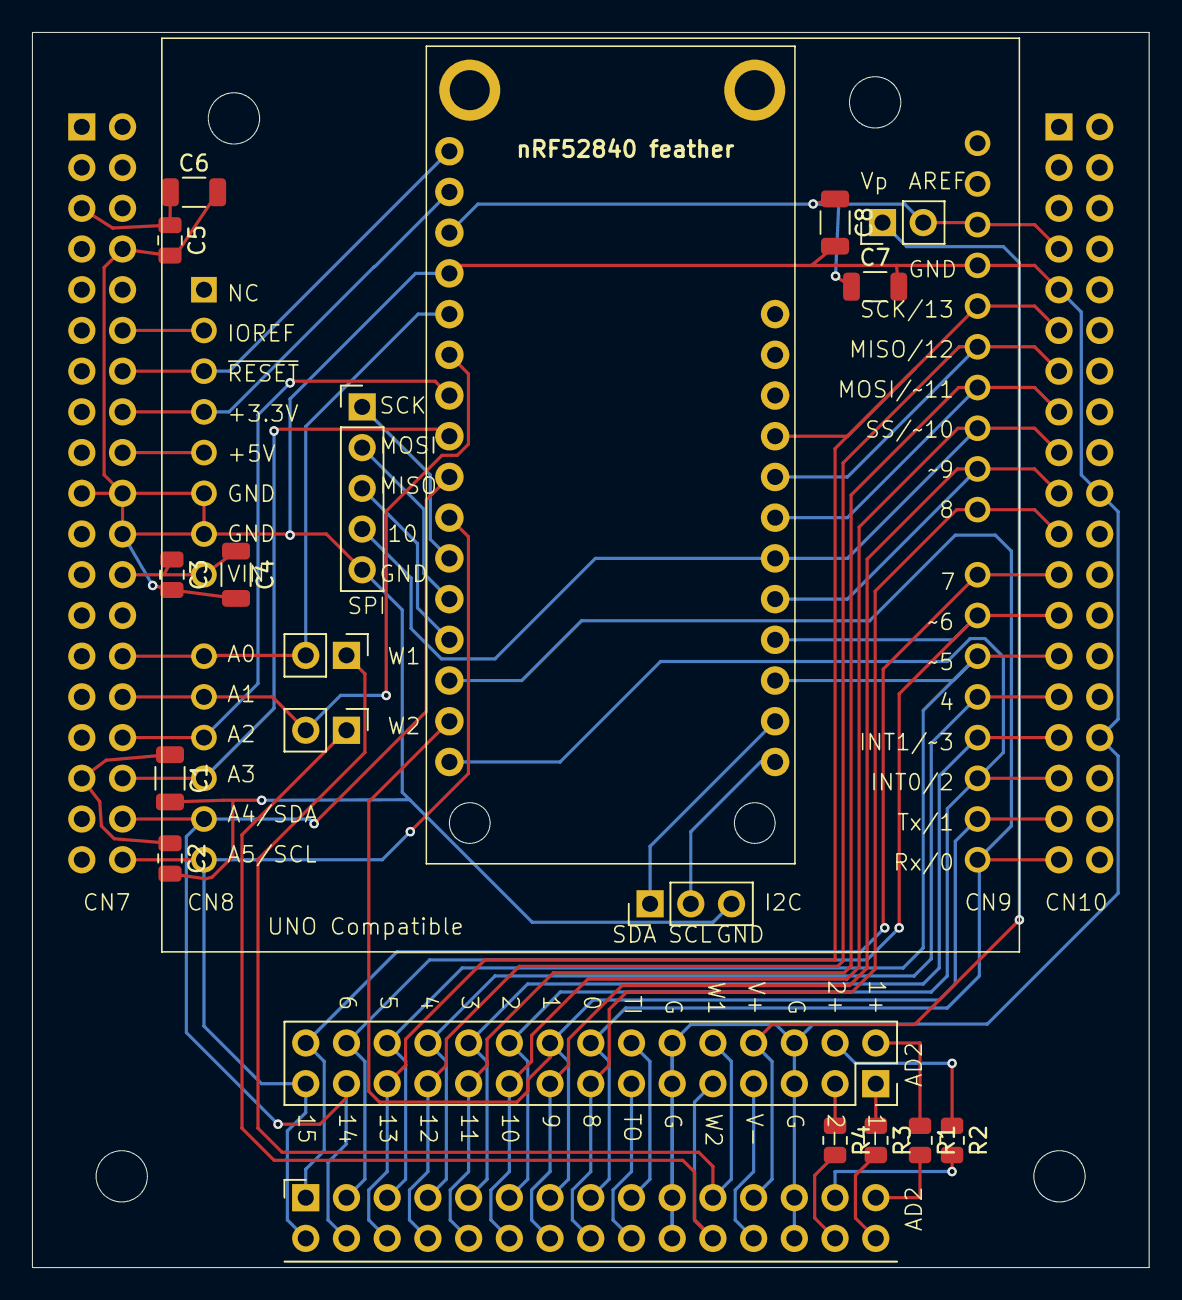
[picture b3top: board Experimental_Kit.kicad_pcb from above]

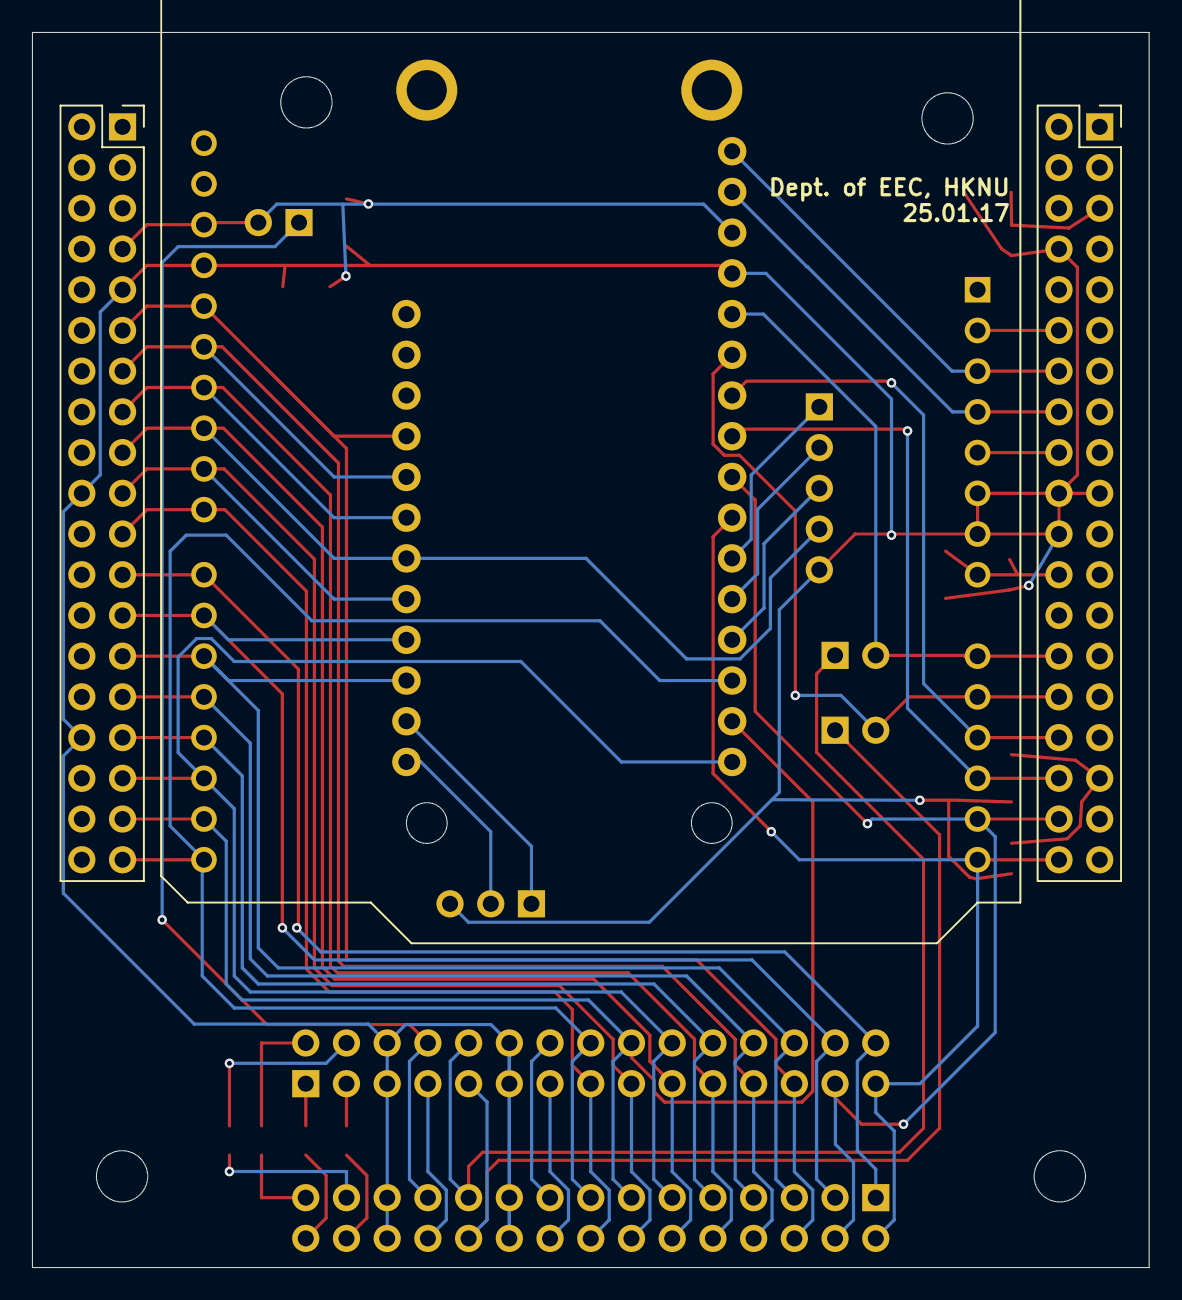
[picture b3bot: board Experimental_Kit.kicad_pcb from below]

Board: 2 copper layers, 69.7 x 77.0 mm, 23 parts (3 on the bottom side), 48 nets.

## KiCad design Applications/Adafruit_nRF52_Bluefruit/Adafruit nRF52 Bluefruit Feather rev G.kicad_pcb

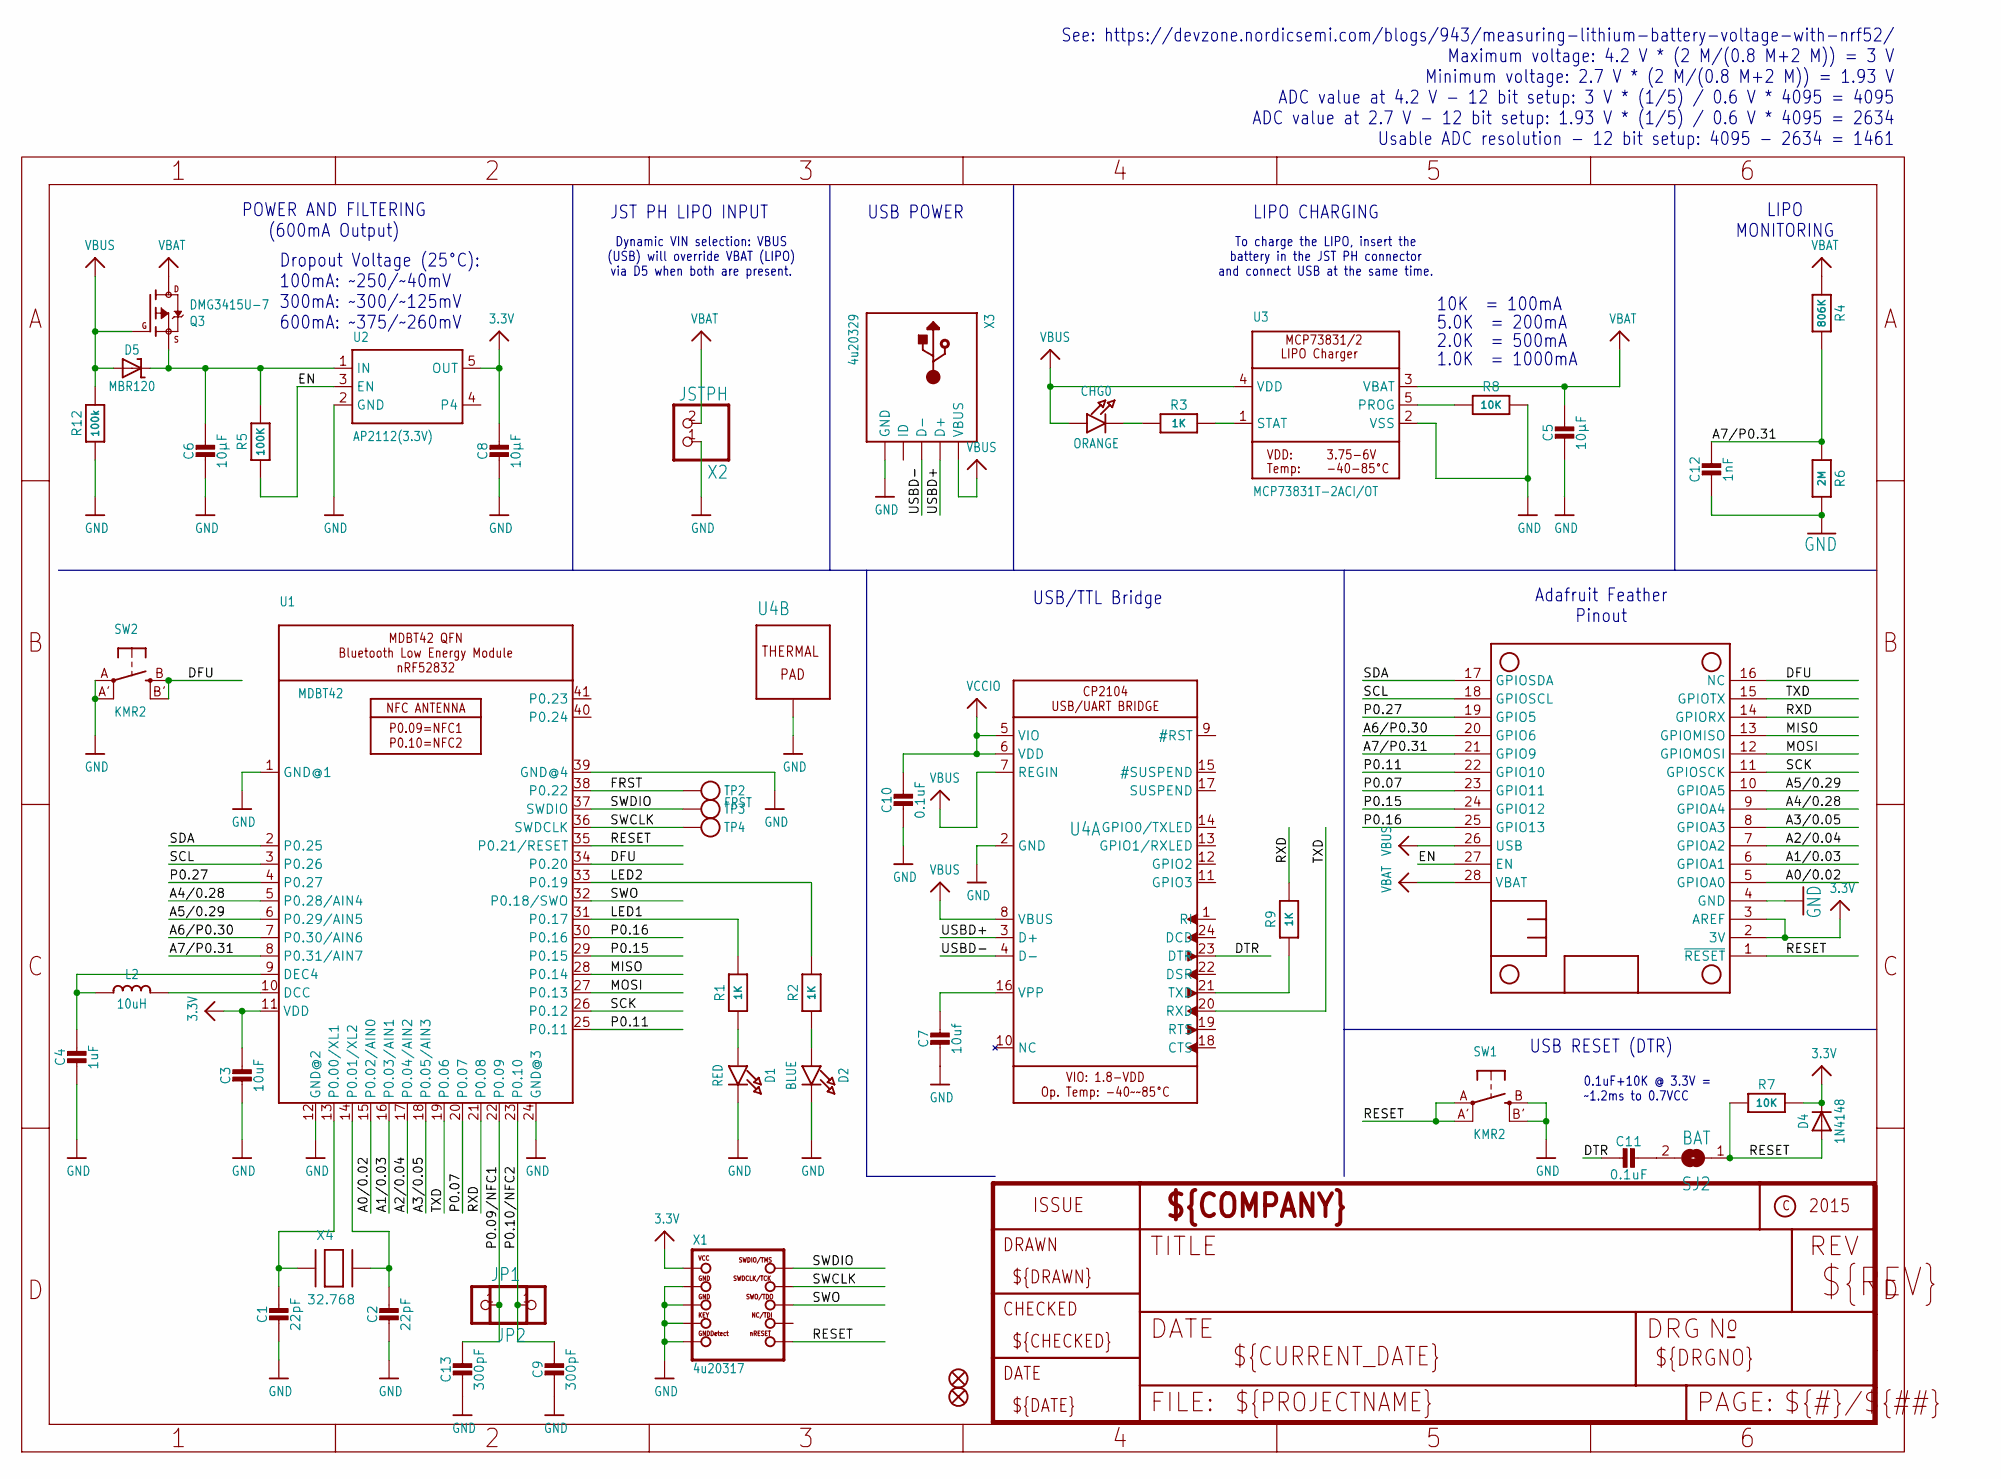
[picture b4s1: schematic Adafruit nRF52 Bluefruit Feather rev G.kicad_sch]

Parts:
C1, C2: 22pF; 0603-NO
C3: 10uF; 0805-NO
C4: 1uF; 0603-NO
C5, C6, C8: 10µF; 0805-NO
C7: 10uf; 0805-NO
C9, C13: 300pF; _0603MP
C10, C11: 0.1uF; 0603-NO
C12: 1nF; 0603-NO
CHG0: ORANGE; CHIPLED_0805_NOOUTLINE
D1: RED; CHIPLED_0805_NOOUTLINE
D2: BLUE; CHIPLED_0805_NOOUTLINE
D4: 1N4148; SOD-323
D5: MBR120; SOD-123
FID1, FID3: FIDUCIAL_1MM
JP1, JP2: HEADER-1X12MM; 1X01_2MM
L2: 10uH; 0805-NO
MS1: FEATHERWING_NODIM
Q3: DMG3415U-7; SOT23-R
R1, R2, R3, R9: 1K; 0603-NO
R4: 806K; 0603-NO
R5: 100K; 0603-NO
R6: 2M; 0603-NO
R7, R8: 10K; 0603-NO
R12: 100k; 0603-NO
SJ2: BAT; SOLDERJUMPER_CLOSEDWIRE
SW1, SW2: KMR2; BTN_KMR2_4.6X2.8
TP2: FRST; PAD-1.5X2.0
TP3, TP4: TESTPOINTROUND2MM; TESTPOINT_ROUND_2MM
U1: MDBT42; BLE_MODULE_RAYTAC_MDBT42
U2: AP2112(3.3V); SOT23-5
U3: MCP73831T-2ACI/OT; SOT23-5
U4: CP2104; QFN24_4MM_SMSC
X1: 4u20317; 2X05_1.27MM_BOX_POSTS
X2: JSTPH; JSTPH2
X3: 4u20329; 4UCONN_20329_V2
X4: 32.768; XTAL3215

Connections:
3.3V: C3.1, C8.1, D4.C, MS1.2 (3V), MS1.3 (AREF), R7.2, U1.11 (VDD), U2.5 (OUT), X1.1 (VCC)
A0/0.02: MS1.5 (GPIOA0), U1.15 (P0.02/AIN0)
A1/0.03: MS1.6 (GPIOA1), U1.16 (P0.03/AIN1)
A2/0.04: MS1.7 (GPIOA2), U1.17 (P0.04/AIN2)
A3/0.05: MS1.8 (GPIOA3), U1.18 (P0.05/AIN3)
A4/0.28: MS1.9 (GPIOA4), U1.5 (P0.28/AIN4)
A5/0.29: MS1.10 (GPIOA5), U1.6 (P0.29/AIN5)
A6/P0.30: MS1.20 (GPIO6), U1.7 (P0.30/AIN6)
A7/P0.31: C12.1, MS1.21 (GPIO9), R4.2, R6.1, U1.8 (P0.31/AIN7)
DFU: MS1.16 (NC), SW2.B (S), SW2.B' (S1), U1.34 (P0.20)
DTR: C11.2, U4.23 (DTR)
EN: MS1.27 (EN), R5.1, U2.3 (EN)
FRST: TP2.P$1, U1.38 (P0.22)
GND: C1.2, C2.2, C3.2, C4.2, C5.2, C6.2, C7.2, C8.2, C9.2, C10.2, C12.2, C13.2, D1.C, D2.C, MS1.4 (GND), R6.2, R8.2, R12.1, SW1.B (S), SW1.B' (S1), SW2.A, SW2.A' (P1), U1.1 (GND@1), U1.12 (GND@2), U1.24 (GND@3), U1.39 (GND@4), U2.2 (GND), U3.2 (VSS), U4.2 (GND), U4.THERM (TP), X1.3 (GND@1), X1.5 (GND@2), X1.7 (KEY), X1.9 (GNDDETECT), X2.1, X3.BASE@1 (GND), X3.BASE@2 (GND), X3.GND, X3.SPRT@1 (GND), X3.SPRT@2 (GND), X3.SPRT@3 (GND), X3.SPRT@4 (GND)
LED1: R1.2, U1.31 (P0.17)
LED2: R2.2, U1.33 (P0.19)
MISO: MS1.13 (GPIOMISO), U1.28 (P0.14)
MOSI: MS1.12 (GPIOMOSI), U1.27 (P0.13)
unnamed: C1.1, U1.13 (P0.00/XL1), X4.P$1
unnamed: C2.1, U1.14 (P0.01/XL2), X4.P$2
unnamed: L2.2, U1.10 (DCC)
unnamed: CHG0.C, R3.1
unnamed: D1.A, R1.1
unnamed: D2.A, R2.1
unnamed: C4.1, L2.1, U1.9 (DEC4)
unnamed: R3.2, U3.1 (STAT)
unnamed: R8.1, U3.5 (PROG)
unnamed: R9.1, U4.21 (TXD)
unnamed: C11.1, SJ2.2
unnamed: C7.1, U4.16 (VPP)
P0.07: MS1.23 (GPIO11), U1.20 (P0.07)
P0.09/NFC1: C13.1, JP2.1, U1.22 (P0.09)
P0.10/NFC2: C9.1, JP1.1, U1.23 (P0.10)
P0.11: MS1.22 (GPIO10), U1.25 (P0.11)
P0.15: MS1.24 (GPIO12), U1.29 (P0.15)
P0.16: MS1.25 (GPIO13), U1.30 (P0.16)
P0.27: MS1.19 (GPIO5), U1.4 (P0.27)
RESET: D4.A, MS1.1 (~RESET), R7.1, SJ2.1, SW1.A, SW1.A' (P1), U1.35 (P0.21/RESET), X1.10 (NRESET)
RXD: MS1.14 (GPIORX), R9.2, U1.21 (P0.08)
SCK: MS1.11 (GPIOSCK), U1.26 (P0.12)
SCL: MS1.18 (GPIOSCL), U1.3 (P0.26)
SDA: MS1.17 (GPIOSDA), U1.2 (P0.25)
SWCLK: TP4.P$1, U1.36 (SWDCLK), X1.4 (SWDCLK)
SWDIO: TP3.P$1, U1.37 (SWDIO), X1.2 (SWDIO)
SWO: U1.32 (P0.18/SWO), X1.6 (SWO)
TXD: MS1.15 (GPIOTX), U1.19 (P0.06), U4.20 (RXD)
USBD+: U4.3 (D+), X3.D+
USBD-: U4.4 (D-), X3.D-
VBAT: C5.1, MS1.28 (VBAT), Q3.3 (D), R4.1, U3.3 (VBAT), X2.2
VBUS: CHG0.A, D5.A, MS1.26 (USB), Q3.1 (G), R12.2, U3.4 (VDD), U4.7 (REGIN), U4.8 (VBUS), X3.VBUS
VCCIO: C10.1, U4.5 (VIO), U4.6 (VDD)
VIN: C6.1, D5.C, Q3.2 (S), R5.2, U2.1 (IN)

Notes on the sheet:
USB/TTL Bridge
LIPO CHARGING
POWER AND FILTERING (600mA Output)
To charge the LIPO, insert the battery in the JST PH connector and connect USB at the same time.
2.0K = 500mA
Dynamic VIN selection: VBUS (USB) will override VBAT (LIPO) via D5 when both are present.
10K = 100mA
See: https://devzone.nordicsemi.com/blogs/943/measuring-lithium-battery-voltage-with-nrf52/ Maximum voltage: 4.2 V * (2 M/(0.8 M+2 M)) = 3 V Minimum voltage: 2.7 V * (2 M/(0.8 M+2 M)) = 1.93 V ADC value at 4.2 V - 12 bit setup: 3 V * (1/5) / 0.6 V * 4095 = 4095 ADC value at 2.7 V - 12 bit setup: 1.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
Adafruit Feather Pinout
5.0K = 200mA
USB RESET (DTR)
0.1uF+10K @ 3.3V = ~1.2ms to 0.7VCC
1.0K = 1000mA
Dropout Voltage (25°C): 100mA: ~250/~40mV 300mA: ~300/~125mV 600mA: ~375/~260mV
JST PH LIPO INPUT
LIPO MONITORING
USB POWER

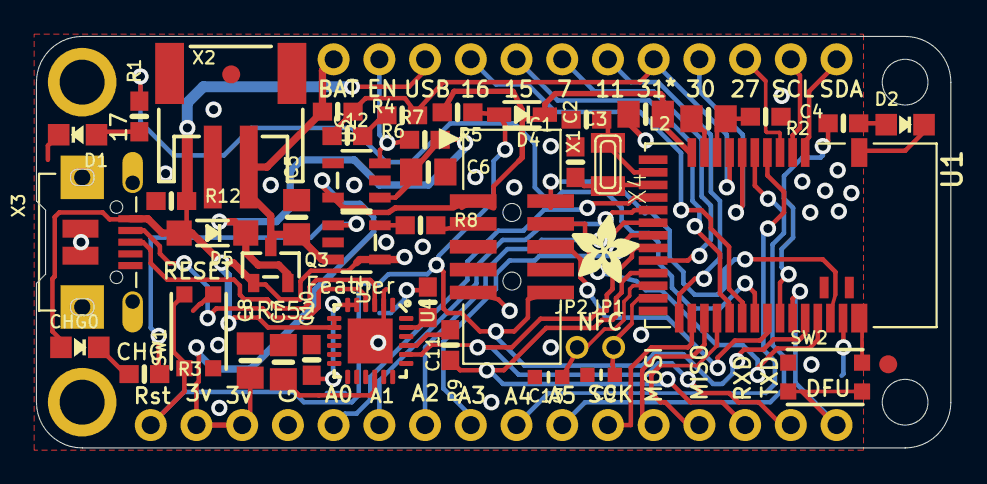
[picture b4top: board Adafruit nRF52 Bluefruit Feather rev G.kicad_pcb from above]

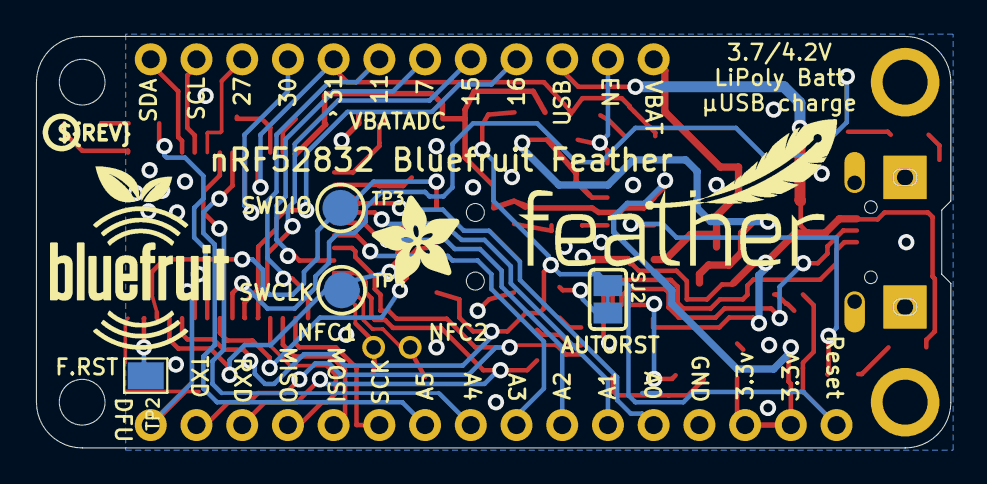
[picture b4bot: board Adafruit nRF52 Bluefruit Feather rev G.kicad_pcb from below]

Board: 2 copper layers, 50.8 x 22.9 mm, 54 parts (8 on the bottom side), 52 nets.

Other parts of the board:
U$17: PCBFEAT-REV-040
U$45: BLUEFRUITLOGO_100MM
U$46: FEATHERLOGO_MED
U$47: ADAFRUIT_5MM
U$49: ADAFRUIT_3.5MM
